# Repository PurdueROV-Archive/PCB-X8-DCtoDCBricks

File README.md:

# PCB-X8-DCtoDCBricks
The high power DC to DC conversion bricks to convert 48V to
manageable levels for thrusters and the power conversion board.
They will also fill in the roll as the motor distribution board.

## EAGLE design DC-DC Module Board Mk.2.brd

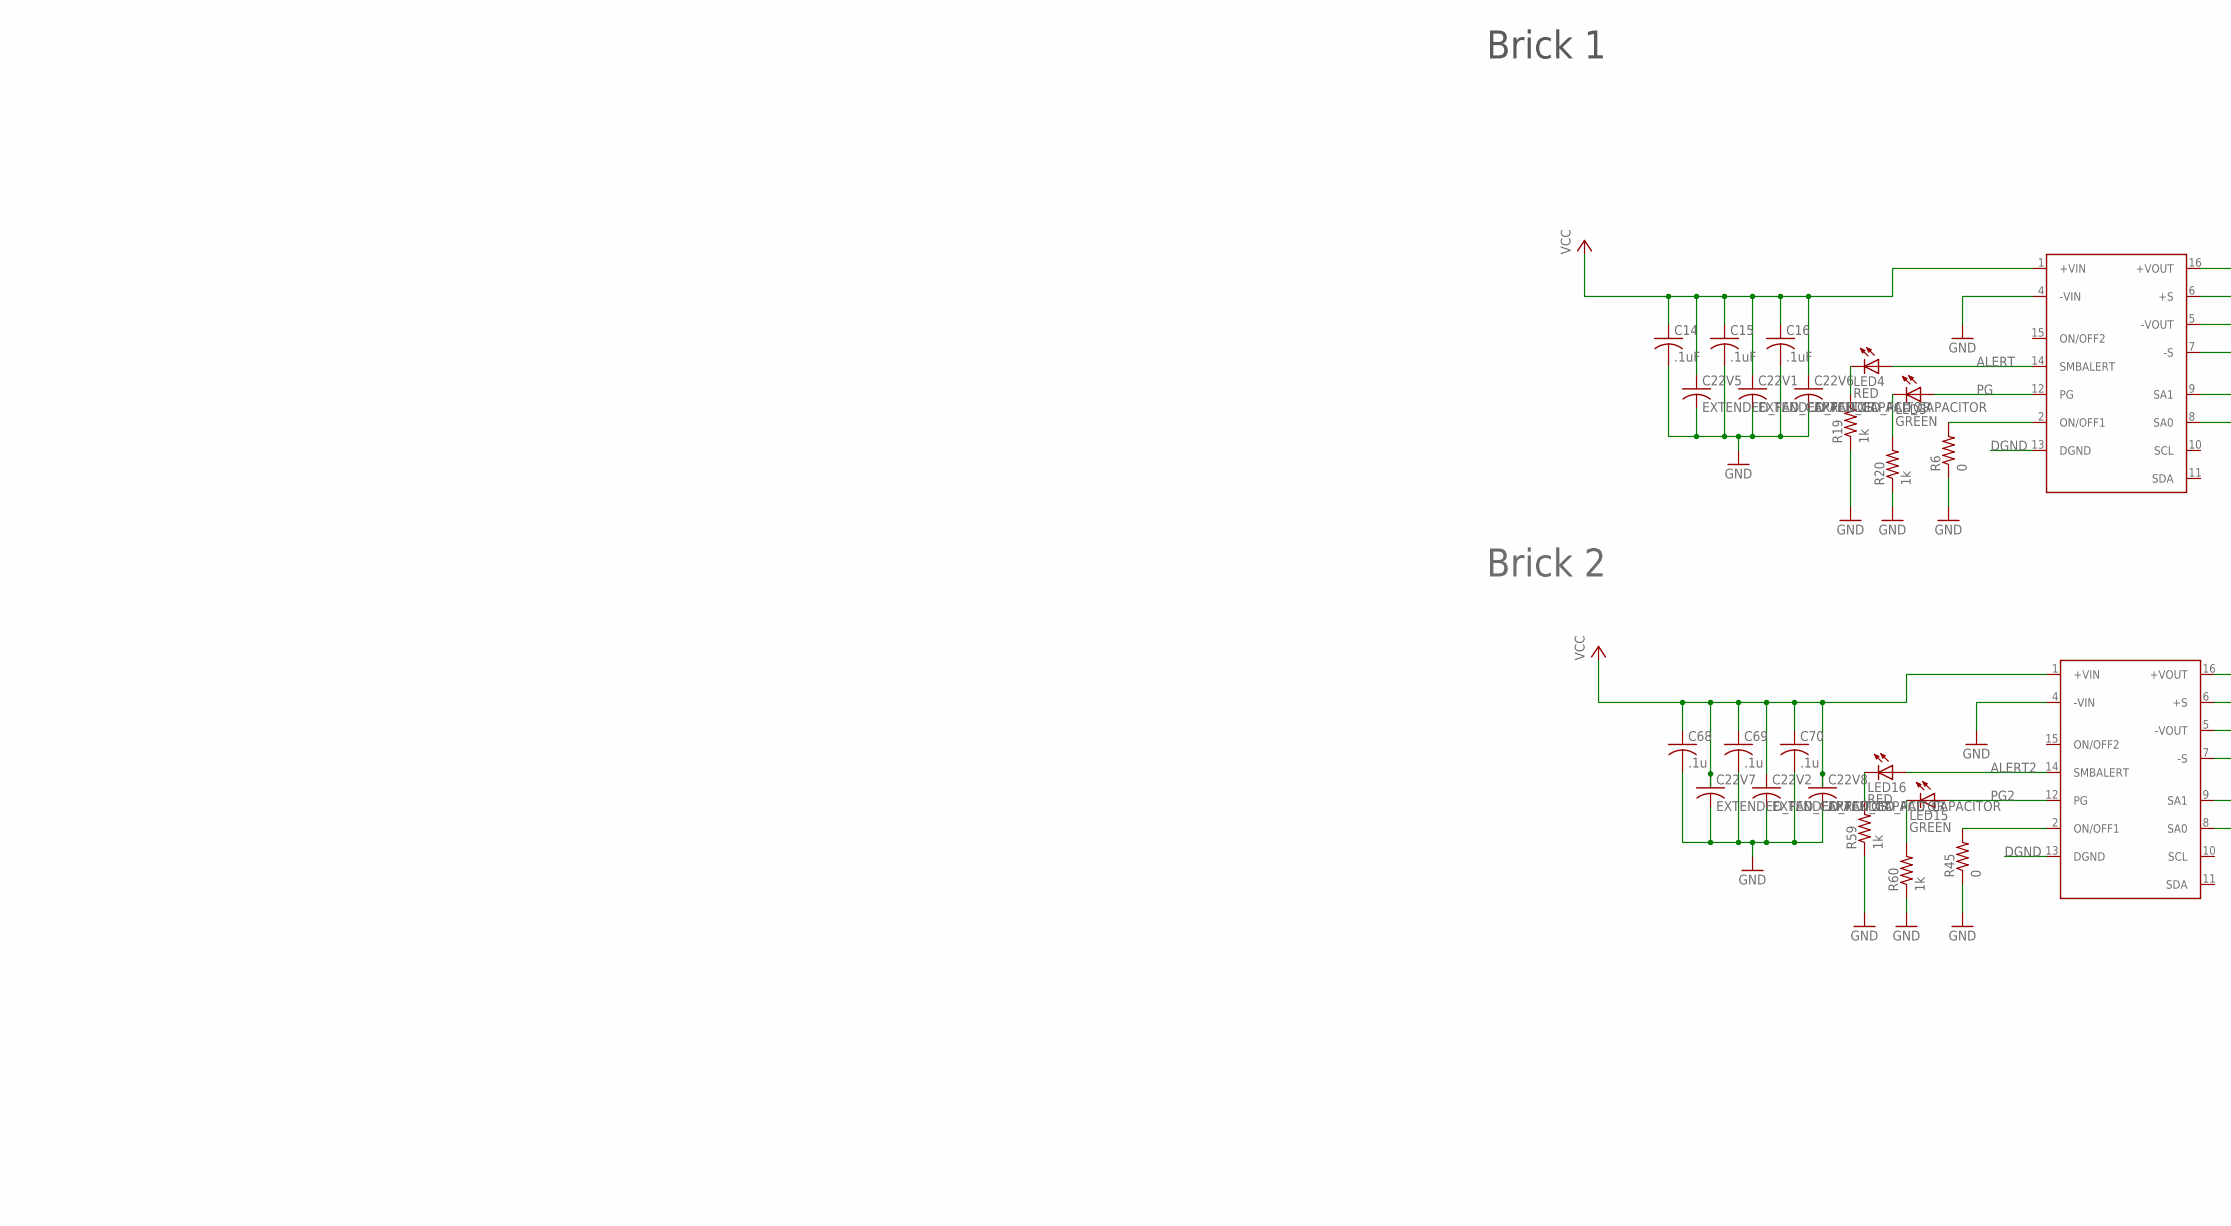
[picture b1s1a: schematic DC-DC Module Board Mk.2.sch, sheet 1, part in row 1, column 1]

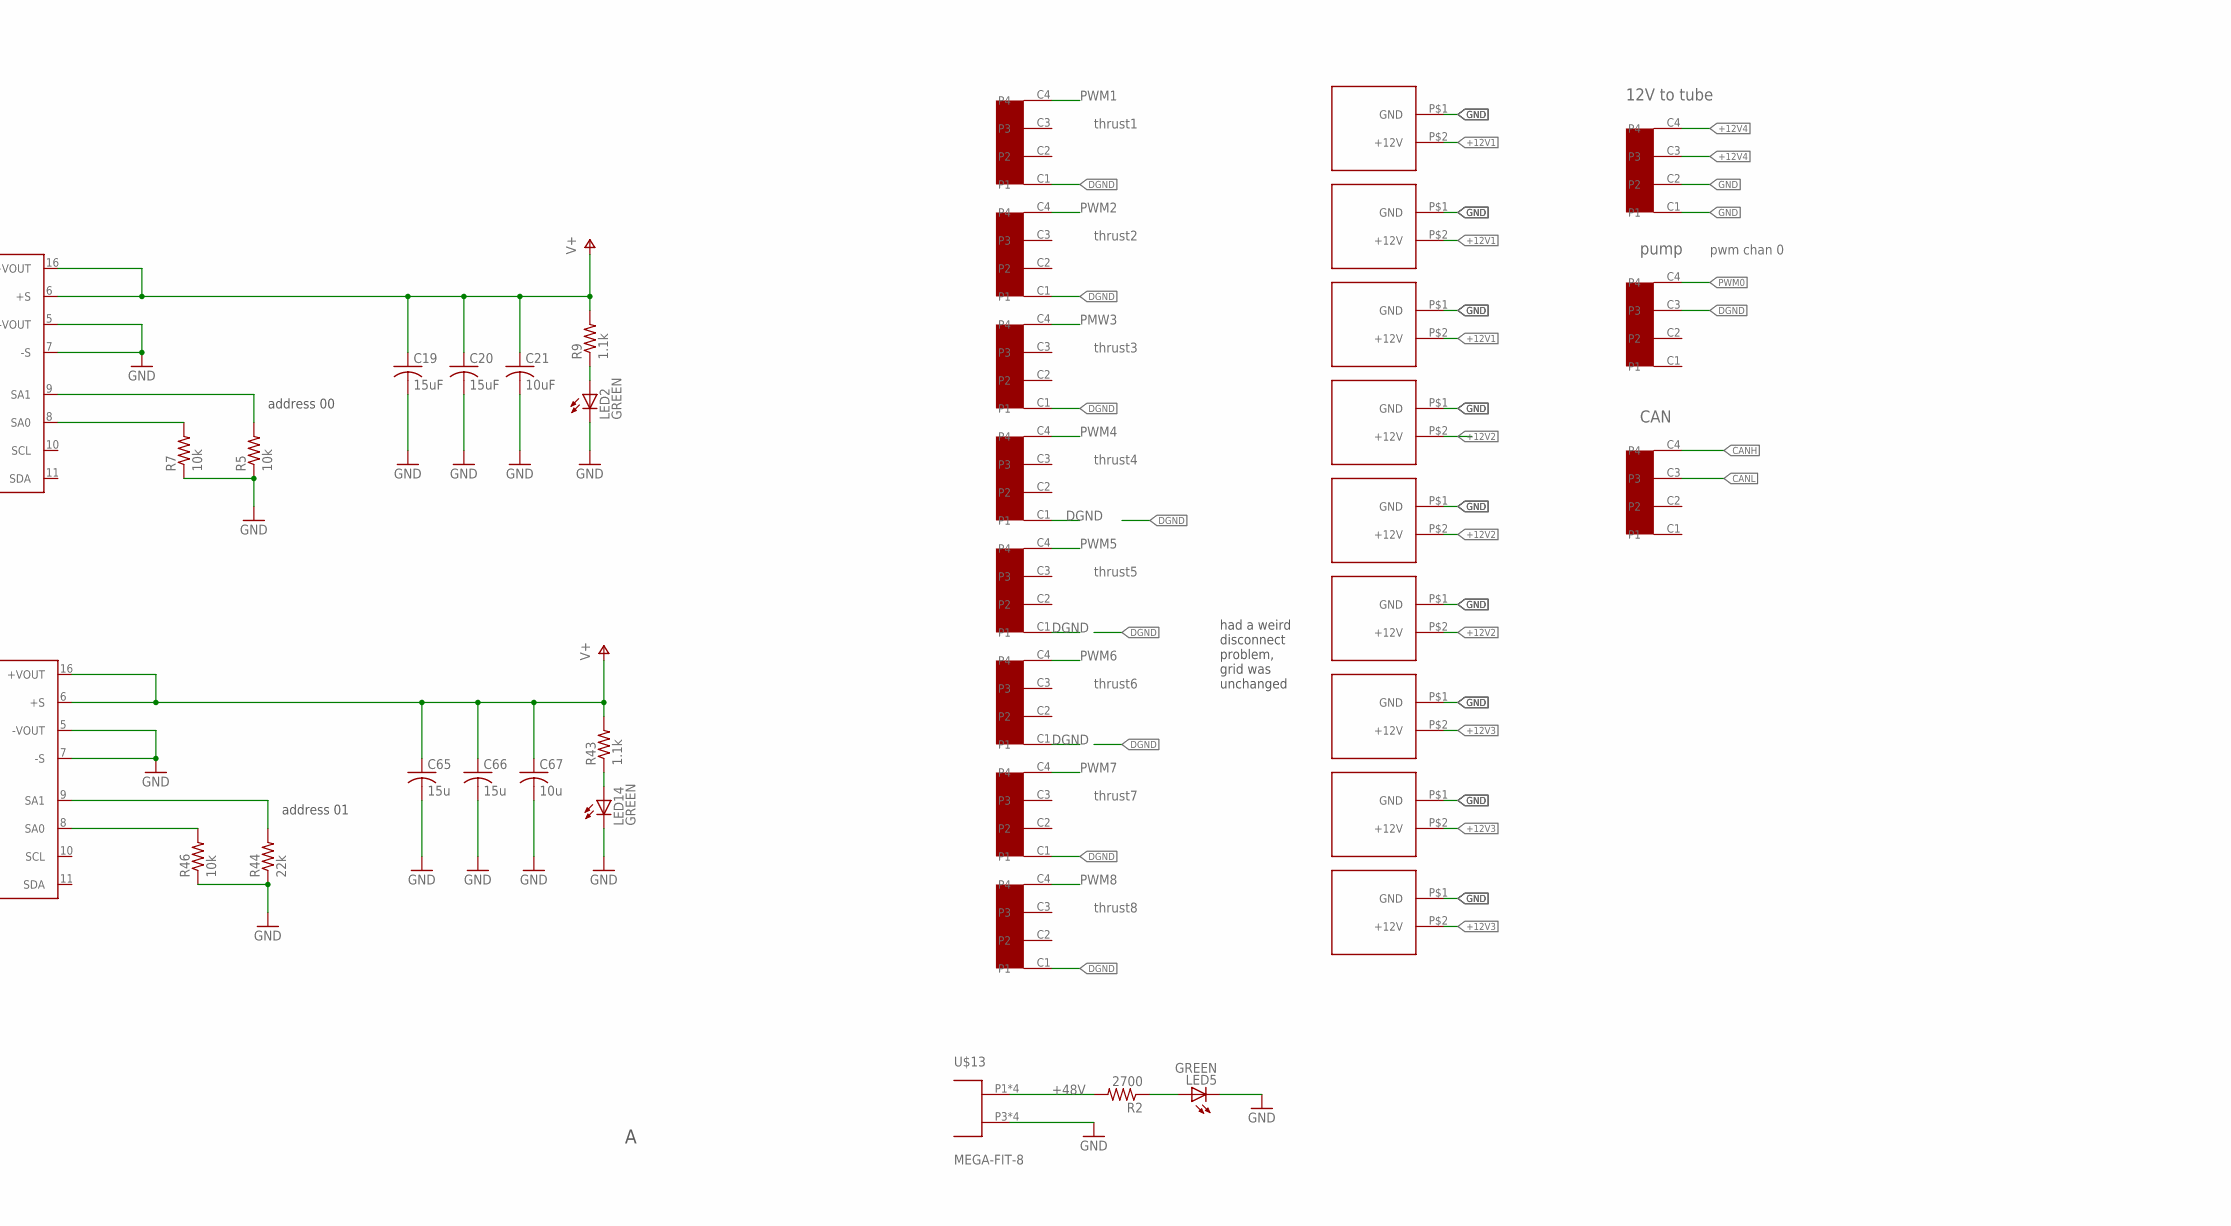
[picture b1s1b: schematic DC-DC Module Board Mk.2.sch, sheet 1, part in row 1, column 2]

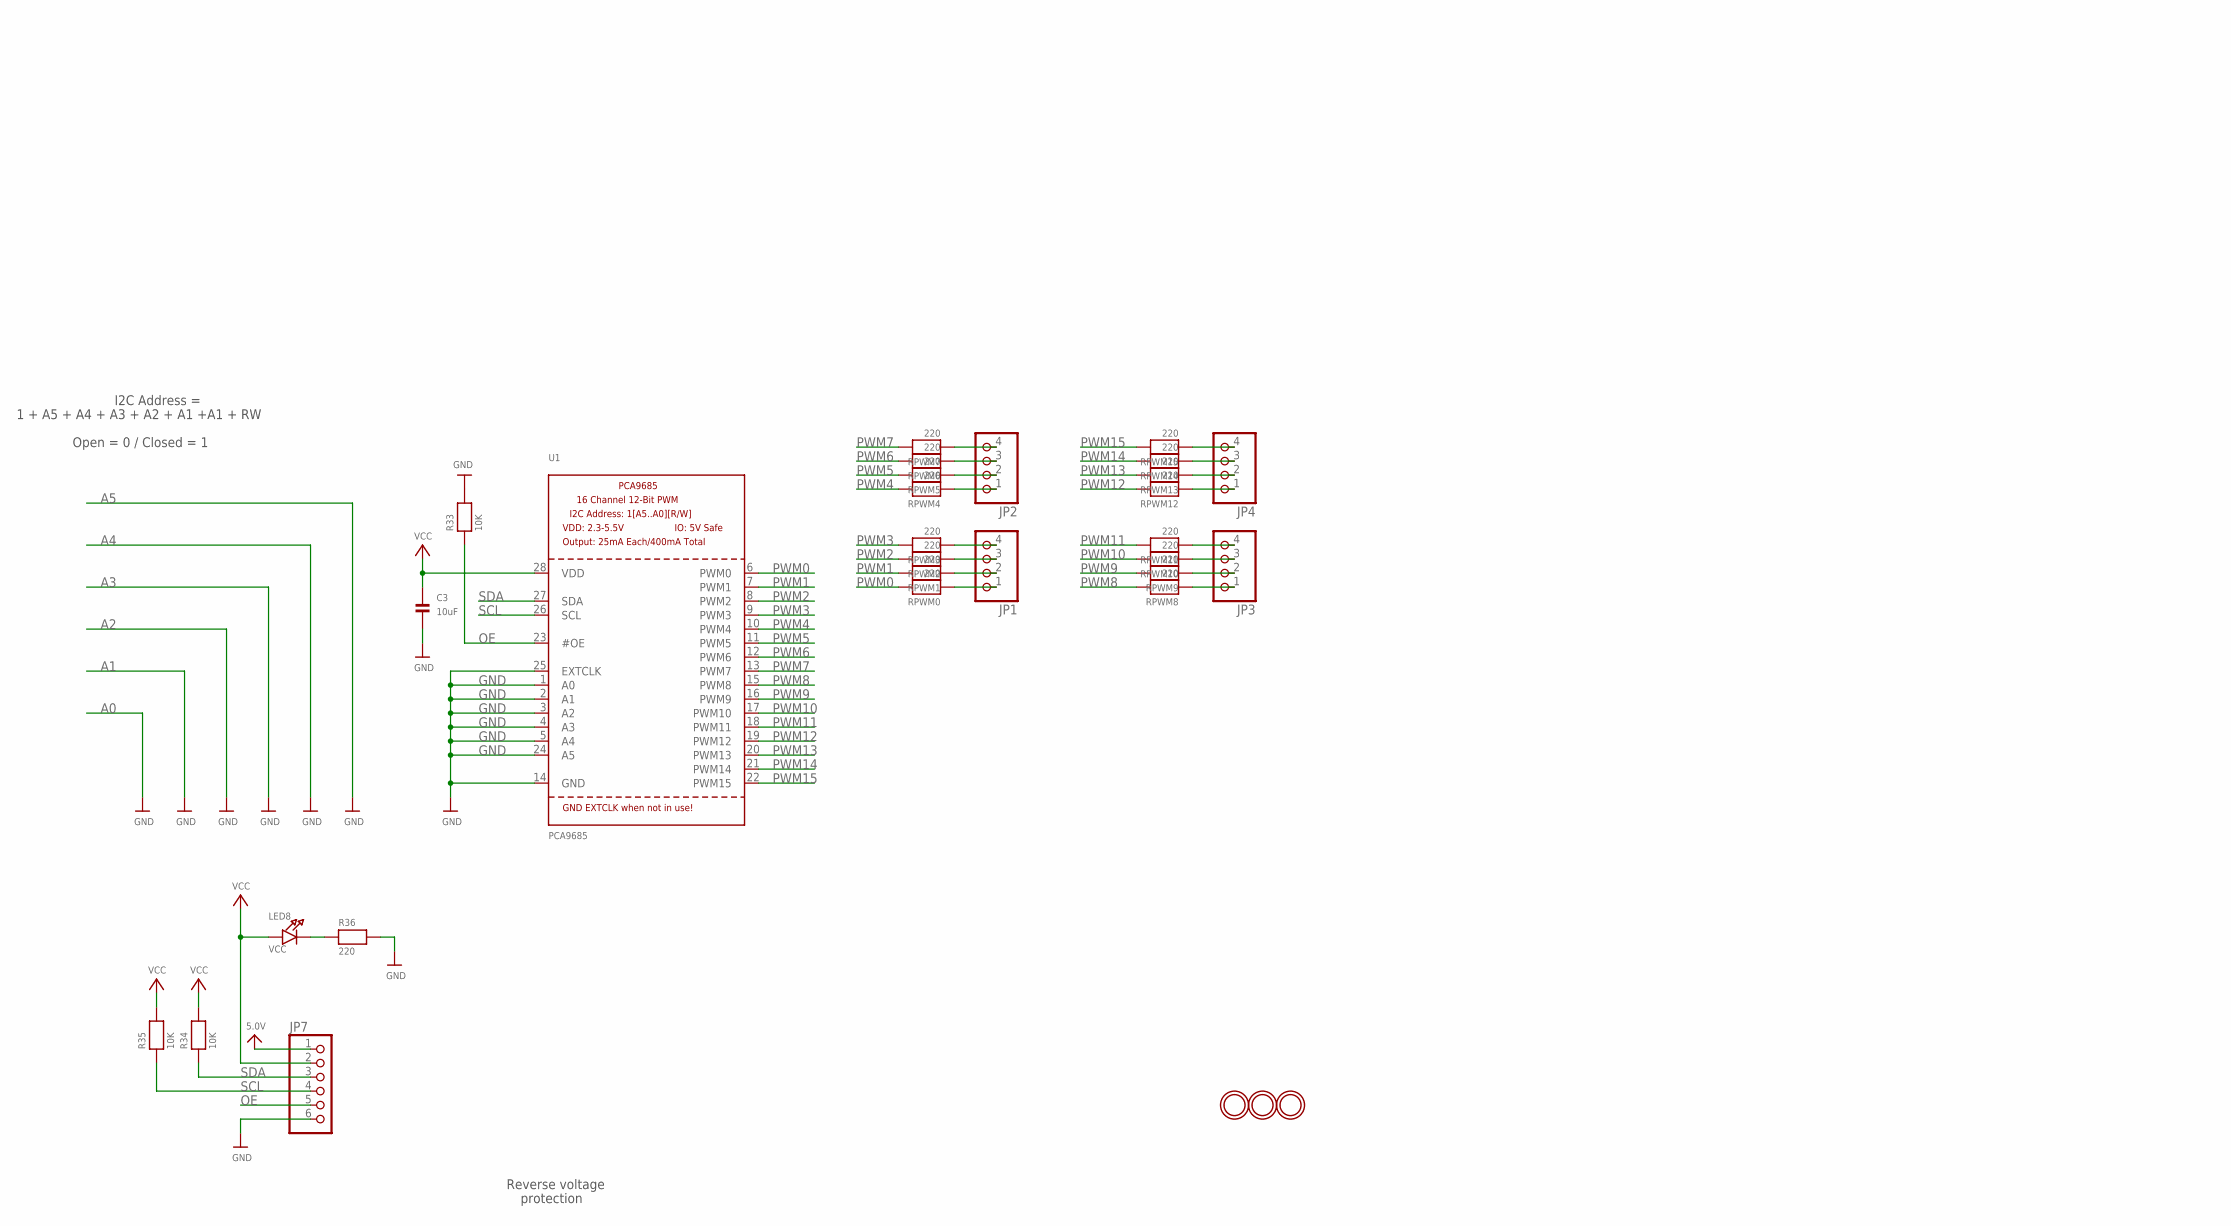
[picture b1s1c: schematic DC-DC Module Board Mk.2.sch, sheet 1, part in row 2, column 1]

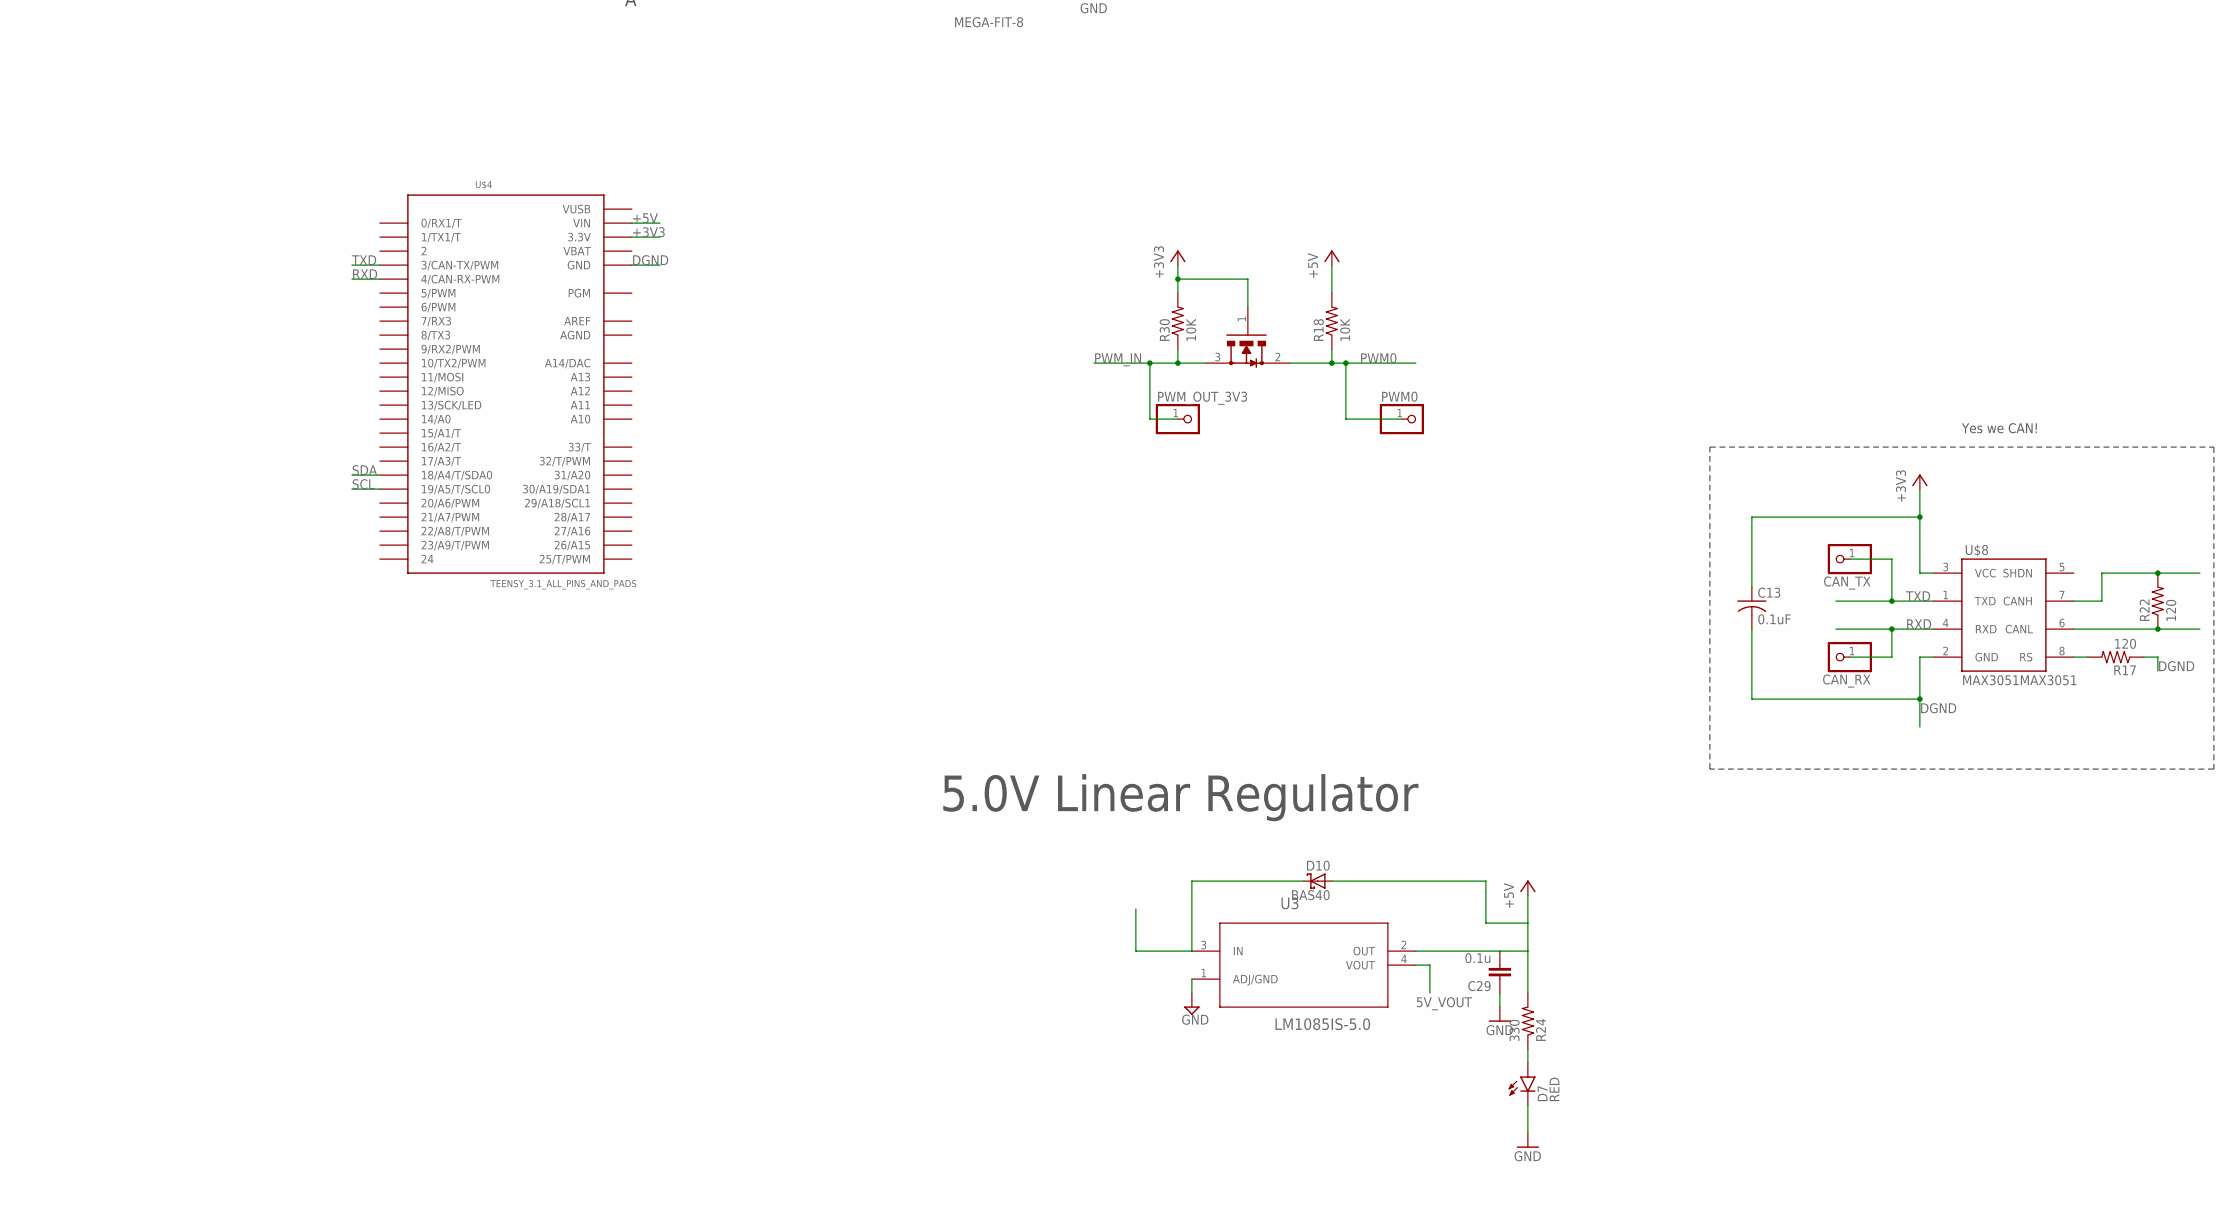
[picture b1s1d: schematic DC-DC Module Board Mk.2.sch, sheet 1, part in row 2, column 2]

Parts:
BRICK1, BRICK2: BRICK_DC-DC_CONVERTER
C3: 10uF; 0805
C13: 0.1uF; C0603
C14, C15, C16: .1uF; C0603
C19, C20: 15uF; C3216
C21: 10uF; C0603
C22V1, C22V2, C22V5, C22V6, C22V7, C22V8: EXTENDED_PAD_CAPACITOR; MODIFIED-NICHICON-UX-8X10
C29: 0.1u; C0603
C65, C66: 15u; C3216
C67: 10u; C0603
C68, C69, C70: .1u; C0603
CAN_RX: PINHD-1X1; 1X01
CAN_TX: PINHD-1X1; 1X01
D7: RED; LED-0603
D10: BAS40; SOT23
JP1, JP2, JP3, JP4: PINHD-1X4; 1X04
JP7: PINHD-1X6CB; 1X06-CLEANBIG
LED2, LED3, LED5, LED14, LED15: GREEN; LED-0603; PARTNO 160-1446-1-ND
LED4, LED16: RED; LED-0603; PARTNO 160-1446-1-ND
LED8: VCC; CHIPLED_0805
PWM0: PINHD-1X1; 1X01
PWM_OUT_3V3: PINHD-1X1; 1X01
R2: 2700; R2512; PARTNO RHC2512FT2K20CT-ND
R5, R7, R46: 10k; R0603; PARTNO 1.00MHCT-ND
R6, R45: 0; R0603; PARTNO 1.00MHCT-ND
R9, R43: 1.1k; R1206; PARTNO RNCP1206FTD1K10CT-ND
R17, R22: 120; R0603
R18, R30: 10K; R0603
R19, R20, R59, R60: 1k; R0603; PARTNO 1.00MHCT-ND
R24: 330; R0603
R33, R34, R35: 10K; 0805
R36: 220; 0805
R44: 22k; R0603; PARTNO 1.00MHCT-ND
RPWM0, RPWM1, RPWM2, RPWM3, RPWM4, RPWM5, RPWM6, RPWM7, RPWM8, RPWM9, RPWM10, RPWM11, RPWM12, RPWM13, RPWM14, RPWM15: 220; 0805
U1: PCA9685; TSSOP28
U3: LM1085IS-5.0; TO254P1435X457-3N
U$2, U$3, U$10, U$11, U$16, U$17, U$18, U$19, U$21: XT60
U$4: TEENSY_3.1_ALL_PINS_AND_PADS; TEENSY3_ALL_PINS_&_PADS
U$8: MAX3051MAX3051; SOT23-8L
U$12: BSS138; SOT-23-BSS138
U$13: MEGA-FIT-8
U$100, U$101, U$102: MOUNTINGHOLE2.5; MOUNTINGHOLE_2.5_PLATED
UFIT0, UFIT1, UFIT2, UFIT3, UFIT4, UFIT5, UFIT6, UFIT7, UFIT8: MICRO-FIT-4-SMD-HZVT; MICRO-FIT-4-SMD(CORRECTED)
UFITCAN: MICRO-FIT-4-SMD-HZVT; MICRO-FIT-4-SMD(CORRECTED)
UFITTUBE: MICRO-FIT-4-SMD-HZVT; MICRO-FIT-4-SMD(CORRECTED)

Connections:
5V_VOUT: U3.4 (VOUT)
+3V3: C13.1, R30.2, U$4.3.3V, U$4.3.3V1 (3.3V), U$4.3.3V2 (3.3V), U$8.3 (VCC), U$12.1 (G)
+5V: C3.1, C29.2, D10.1 (A), JP7.1, JP7.2, LED8.A, R18.2, R24.2, R34.2, R35.2, U1.28 (VDD), U3.2 (OUT), U$4.VIN
+12V1: BRICK1.6 (+S), BRICK1.16 (+VOUT), C19.1, C20.1, C21.1, R9.2, U$2.P$2 (+12V), U$3.P$2 (+12V), U$10.P$2 (+12V)
+12V2: BRICK2.6 (+S), BRICK2.16 (+VOUT), C65.1, C66.1, C67.1, R43.2, U$11.P$2 (+12V), U$16.P$2 (+12V), U$17.P$2 (+12V)
+12V3: U$18.P$2 (+12V), U$19.P$2 (+12V), U$21.P$2 (+12V); also elsewhere on the board
+12V4: D10.3 (C), U3.3 (IN), UFITTUBE.C3 (P3), UFITTUBE.C4 (P4); also elsewhere on the board
+48V: BRICK1.1 (+VIN), BRICK2.1 (+VIN), C14.1, C15.1, C16.1, C22V1.P$3 (3), C22V2.P$3 (3), C22V5.P$3 (3), C22V6.P$3 (3), C22V7.P$3 (3), C22V8.P$3 (3), C68.1, C69.1, C70.1, R2.2, U$13.P1, U$13.P2, U$13.P5, U$13.P6; also elsewhere on the board
ADRS00A: BRICK1.8 (SA0), R7.2
ADRS00A4: BRICK2.8 (SA0), R46.2
ADRS00B: BRICK1.9 (SA1), R5.2
ADRS00B4: BRICK2.9 (SA1), R44.2
AGND: U$4.AGND
ALERT: BRICK1.14 (SMBALERT), LED4.A
ALERT2: BRICK2.14 (SMBALERT), LED16.A
AREF: U$4.AREF
CANH: R22.2, U$8.7 (CANH), UFITCAN.C4 (P4)
CANL: R22.1, U$8.6 (CANL), UFITCAN.C3 (P3)
DGND: BRICK1.13 (DGND), BRICK2.13 (DGND), C13.2, R17.1, U$4.GND, U$4.GND1 (GND), U$4.GND2 (GND), U$8.2 (GND), UFIT0.C1 (P1), UFIT1.C1 (P1), UFIT2.C3 (P3), UFIT3.C1 (P1), UFIT4.C1 (P1), UFIT5.C1 (P1), UFIT6.C1 (P1), UFIT7.C1 (P1), UFIT8.C1 (P1); also elsewhere on the board
GND: BRICK1.4 (-VIN), BRICK1.5 (-VOUT), BRICK1.7 (-S), BRICK2.4 (-VIN), BRICK2.5 (-VOUT), BRICK2.7 (-S), C3.2, C14.2, C15.2, C16.2, C19.2, C20.2, C21.2, C22V1.P$1 (4), C22V2.P$1 (4), C22V5.P$1 (4), C22V6.P$1 (4), C22V7.P$1 (4), C22V8.P$1 (4), C29.1, C65.2, C66.2, C67.2, C68.2, C69.2, C70.2, D7.C, JP7.6, LED2.C, LED5.C, LED14.C, R5.1, R6.1, R7.1, R19.1, R20.1, R33.2, R36.2, R44.1, R45.1, R46.1, R59.1, R60.1, U1.1 (A0), U1.2 (A1), U1.3 (A2), U1.4 (A3), U1.5 (A4), U1.14 (GND), U1.24 (A5), U1.25 (EXTCLK), U3.1 (ADJ/GND), U$2.P$1 (GND), U$3.P$1 (GND), U$10.P$1 (GND), U$11.P$1 (GND), U$13.P3, U$13.P4, U$13.P7, U$13.P8, U$16.P$1 (GND), U$17.P$1 (GND), U$18.P$1 (GND), U$19.P$1 (GND), U$21.P$1 (GND), UFITTUBE.C1 (P1), UFITTUBE.C2 (P2); also elsewhere on the board
unnamed: BRICK1.2 (ON/OFF1), R6.2
unnamed: LED5.A, R2.1
unnamed: LED4.C, R19.2
unnamed: LED3.C, R20.2
unnamed: LED2.A, R9.1
unnamed: LED8.C, R36.1
unnamed: JP2.3, RPWM6.1
unnamed: JP2.4, RPWM7.1
unnamed: JP2.2, RPWM5.1
unnamed: D7.A, R24.1
unnamed: LED14.A, R43.1
unnamed: JP2.1, RPWM4.1
unnamed: BRICK2.2 (ON/OFF1), R45.2
unnamed: JP1.4, RPWM3.1
unnamed: JP1.3, RPWM2.1
unnamed: JP1.2, RPWM1.1
unnamed: JP1.1, RPWM0.1
unnamed: JP3.1, RPWM8.1
unnamed: JP3.2, RPWM9.1
unnamed: JP3.3, RPWM10.1
unnamed: LED16.C, R59.2
unnamed: LED15.C, R60.2
unnamed: JP3.4, RPWM11.1
unnamed: JP4.1, RPWM12.1
unnamed: JP4.2, RPWM13.1
unnamed: JP4.3, RPWM14.1
unnamed: JP4.4, RPWM15.1
unnamed: R17.2, U$8.8 (RS)
OE: JP7.5, R33.1, U1.23 (#OE)
PG: BRICK1.12 (PG), LED3.A
PG2: BRICK2.12 (PG), LED15.A
PMW3: UFIT3.C4 (P4)
PWM0: PWM0.1, R18.1, RPWM0.2, U1.6 (PWM0), U$12.2 (D), UFIT2.C4 (P4)
PWM1: RPWM1.2, U1.7 (PWM1), UFIT1.C4 (P4)
PWM2: RPWM2.2, U1.8 (PWM2), UFIT0.C4 (P4)
PWM3: RPWM3.2, U1.9 (PWM3)
PWM4: RPWM4.2, U1.10 (PWM4), UFIT4.C4 (P4)
PWM5: RPWM5.2, U1.11 (PWM5), UFIT5.C4 (P4)
PWM6: RPWM6.2, U1.12 (PWM6), UFIT6.C4 (P4)
PWM7: RPWM7.2, U1.13 (PWM7), UFIT7.C4 (P4)
PWM8: RPWM8.2, U1.15 (PWM8), UFIT8.C4 (P4)
PWM9: RPWM9.2, U1.16 (PWM9)
PWM10: RPWM10.2, U1.17 (PWM10)
PWM11: RPWM11.2, U1.18 (PWM11)
PWM12: RPWM12.2, U1.19 (PWM12)
PWM13: RPWM13.2, U1.20 (PWM13)
PWM14: RPWM14.2, U1.21 (PWM14)
PWM15: RPWM15.2, U1.22 (PWM15)
PWM_IN: PWM_OUT_3V3.1, R30.1, U$12.3 (S)
RXD: CAN_RX.1, U$4.4 (4/CAN-RX-PWM), U$8.4 (RXD)
SCL: JP7.4, R35.1, U1.26 (SCL), U$4.19/A5 (19/A5/T/SCL0)
SDA: JP7.3, R34.1, U1.27 (SDA), U$4.18/A4 (18/A4/T/SDA0)
TXD: CAN_TX.1, U$4.3 (3/CAN-TX/PWM), U$8.1 (TXD)
VBAT: U$4.VBAT
VUSB: U$4.VUSB

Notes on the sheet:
address 00
Yes we CAN!
Brick 1
5.0V Linear Regulator
Brick 2
address 01
12V to tube
pump
CAN
Reverse voltage
protection
1 + A5 + A4 + A3 + A2 + A1 +A1 + RW
I2C Address =
Open = 0 / Closed = 1
thrust2
thrust1
thrust3
thrust4
thrust5
thrust6
thrust7
thrust8
pwm chan 0
had a weird disconnect problem, grid was unchanged

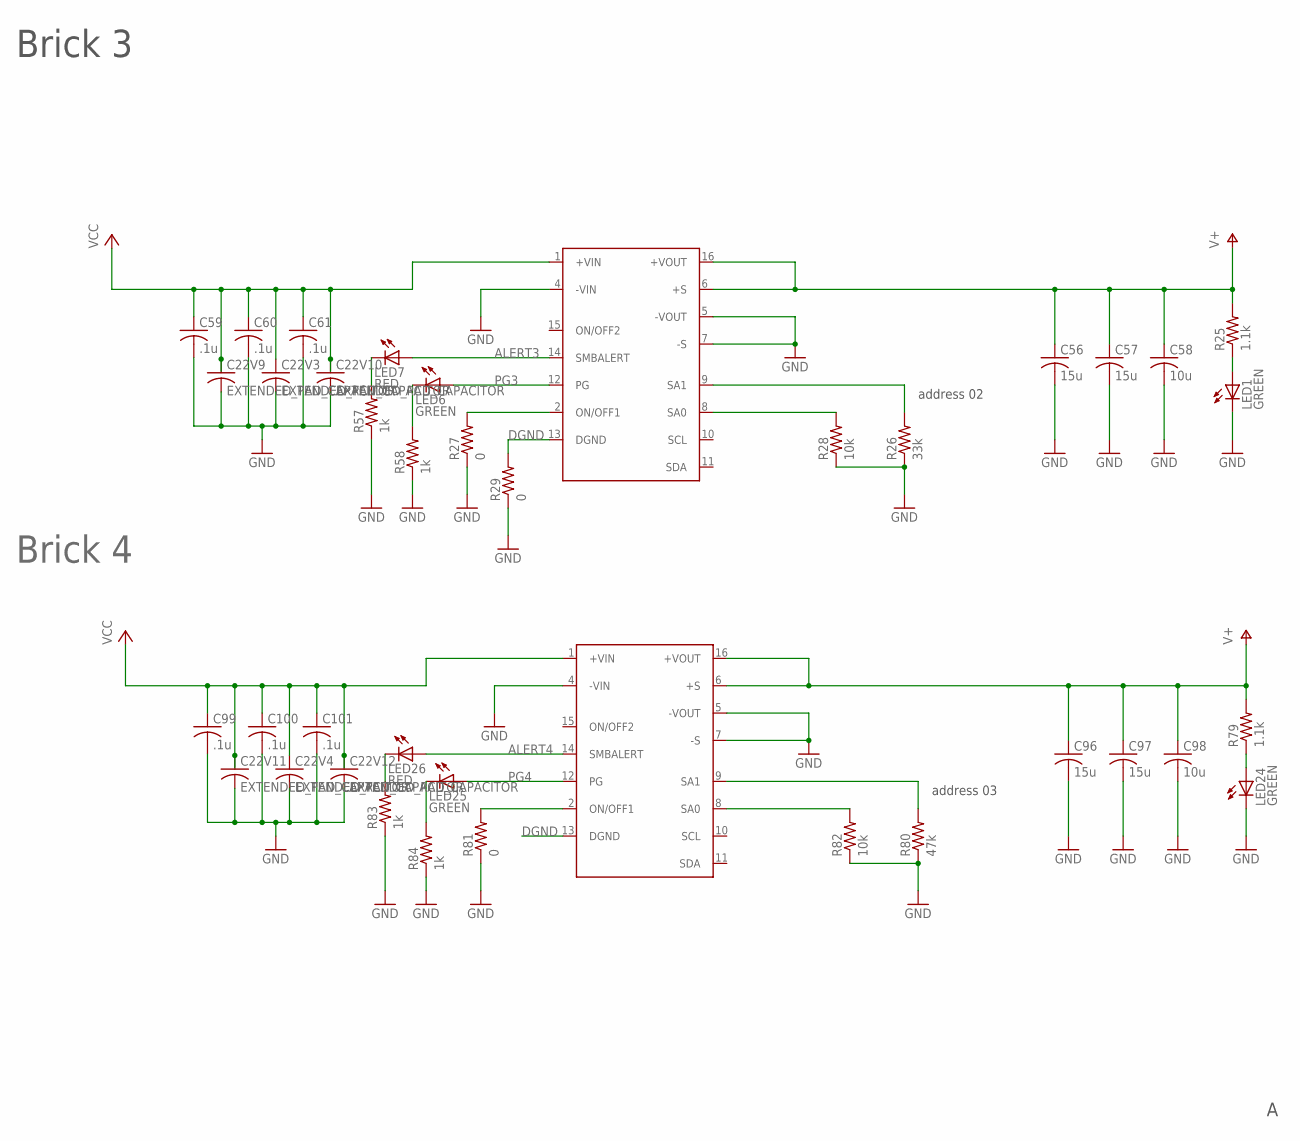
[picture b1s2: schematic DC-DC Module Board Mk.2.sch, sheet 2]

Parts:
BRICK3, BRICK4: BRICK_DC-DC_CONVERTER
C22V3, C22V4, C22V9, C22V10, C22V11, C22V12: EXTENDED_PAD_CAPACITOR; MODIFIED-NICHICON-UX-8X10
C56, C57, C96, C97: 15u; C3216
C58, C98: 10u; C0603
C59, C60, C61, C99, C100, C101: .1u; C0603
LED1, LED6, LED24, LED25: GREEN; LED-0603; PARTNO 160-1446-1-ND
LED7, LED26: RED; LED-0603; PARTNO 160-1446-1-ND
R25, R79: 1.1k; R1206; PARTNO RNCP1206FTD1K10CT-ND
R26: 33k; R0603; PARTNO 1.00MHCT-ND
R27, R29, R81: 0; R0603; PARTNO 1.00MHCT-ND
R28, R82: 10k; R0603; PARTNO 1.00MHCT-ND
R57, R58, R83, R84: 1k; R0603; PARTNO 1.00MHCT-ND
R80: 47k; R0603; PARTNO 1.00MHCT-ND

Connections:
+12V3: BRICK3.6 (+S), BRICK3.16 (+VOUT), C56.1, C57.1, C58.1, R25.2; also elsewhere on the board
+12V4: BRICK4.6 (+S), BRICK4.16 (+VOUT), C96.1, C97.1, C98.1, R79.2; also elsewhere on the board
+48V: BRICK3.1 (+VIN), BRICK4.1 (+VIN), C22V3.P$3 (3), C22V4.P$3 (3), C22V9.P$3 (3), C22V10.P$3 (3), C22V11.P$3 (3), C22V12.P$3 (3), C59.1, C60.1, C61.1, C99.1, C100.1, C101.1; also elsewhere on the board
ADRS00A1: BRICK3.8 (SA0), R28.2
ADRS00A5: BRICK4.8 (SA0), R82.2
ADRS00B1: BRICK3.9 (SA1), R26.2
ADRS00B5: BRICK4.9 (SA1), R80.2
ALERT3: BRICK3.14 (SMBALERT), LED7.A
ALERT4: BRICK4.14 (SMBALERT), LED26.A
DGND: BRICK3.13 (DGND), BRICK4.13 (DGND), R29.2; also elsewhere on the board
GND: BRICK3.4 (-VIN), BRICK3.5 (-VOUT), BRICK3.7 (-S), BRICK4.4 (-VIN), BRICK4.5 (-VOUT), BRICK4.7 (-S), C22V3.P$1 (4), C22V4.P$1 (4), C22V9.P$1 (4), C22V10.P$1 (4), C22V11.P$1 (4), C22V12.P$1 (4), C56.2, C57.2, C58.2, C59.2, C60.2, C61.2, C96.2, C97.2, C98.2, C99.2, C100.2, C101.2, LED1.C, LED24.C, R26.1, R27.1, R28.1, R29.1, R57.1, R58.1, R80.1, R81.1, R82.1, R83.1, R84.1; also elsewhere on the board
unnamed: LED1.A, R25.1
unnamed: BRICK3.2 (ON/OFF1), R27.2
unnamed: LED7.C, R57.2
unnamed: LED6.C, R58.2
unnamed: LED24.A, R79.1
unnamed: BRICK4.2 (ON/OFF1), R81.2
unnamed: LED26.C, R83.2
unnamed: LED25.C, R84.2
PG3: BRICK3.12 (PG), LED6.A
PG4: BRICK4.12 (PG), LED25.A

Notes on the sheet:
address 02
Brick 3
Brick 4
address 03

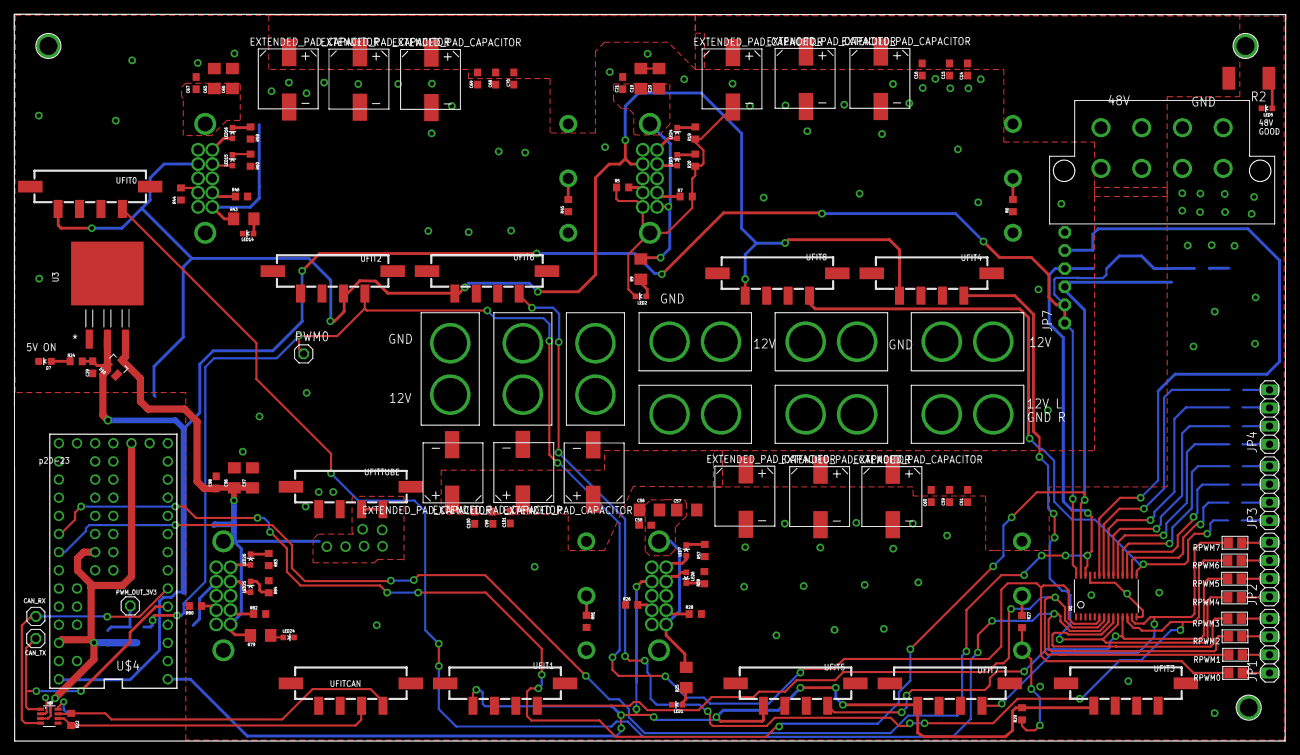
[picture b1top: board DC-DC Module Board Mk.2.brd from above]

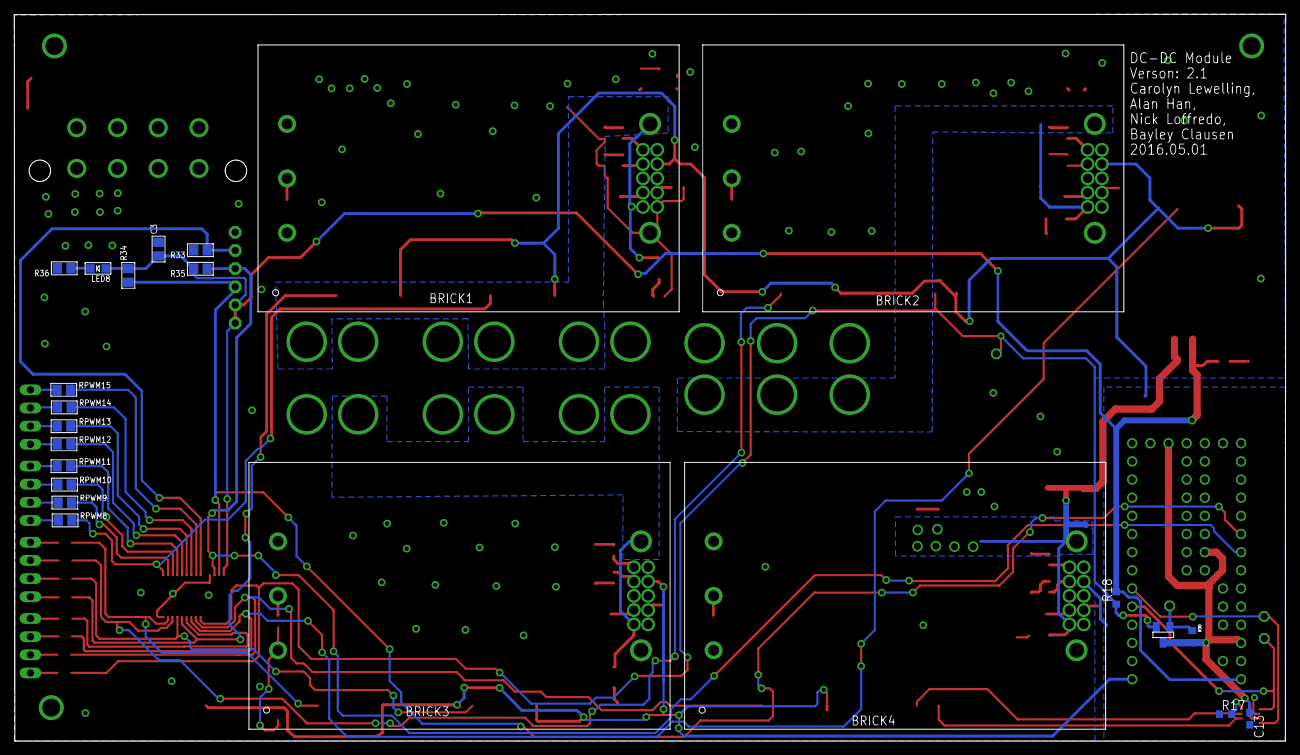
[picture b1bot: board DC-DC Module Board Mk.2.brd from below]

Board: 2 copper layers, 177.9 x 101.7 mm, 148 parts (23 on the bottom side), 85 nets.

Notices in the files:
parts and their libraries:
SparkFun: Licensing: CC v3.0 Share-Alike You are welcome to use this library for commercial purposes.
SparkFun-LED: Licensing: Creative Commons ShareAlike 4.0 International - https://creativecommons.org/licenses/by-sa/4.0
